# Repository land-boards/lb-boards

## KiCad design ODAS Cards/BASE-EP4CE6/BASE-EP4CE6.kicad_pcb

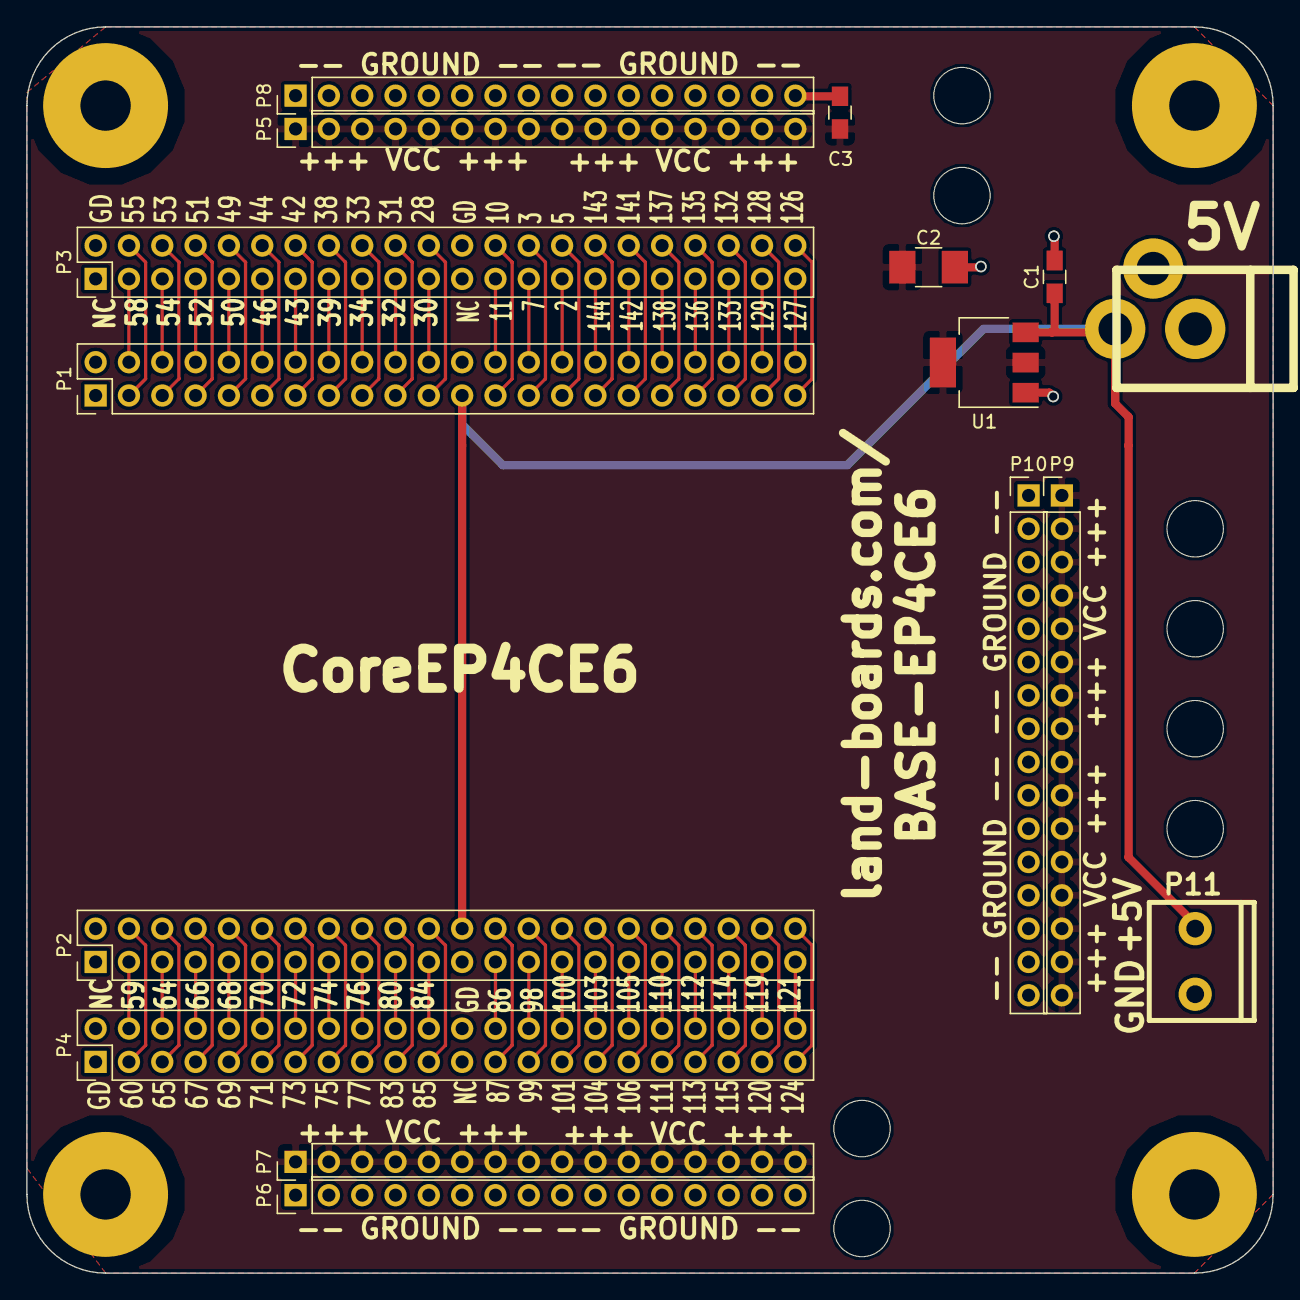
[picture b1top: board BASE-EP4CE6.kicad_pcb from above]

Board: 2 copper layers, 95.0 x 95.0 mm, 30 parts (0 on the bottom side), 83 nets.

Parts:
C1, C3: 0.1uF; C_0805_HandSoldering
C2: 10uF; C_1210_HandSoldering
COUP?1: COUPON; TEST_BLK-REAR
J1: DCJ0202; DCJ-NEW
MTG1, MTG2, MTG3: MTG_HOLE; MTG-6-32
MTG6, MTG7, MTG9, MTG10, MTG12, MTG13, MTG14, MTG15: MTG_HOLE; MountingHole_4.3mm_M4
MTG?1: MTG_HOLE; MTG-6-32
P1, P2, P3, P4: CONN_02X22; Pin_Header_Straight_2x22_Pitch2.54mm
P5, P6, P7, P8, P9, P10: CONN_01X16; Pin_Header_Straight_1x16_Pitch2.54mm
P11: CONN_01X02; TB2-5MM
TEST: COUPON; TEST_BLK-REAR
U1: AP1117; SOT-223

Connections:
+3V3: C2.1, C3.1, P5.1, P5.2, P5.3, P5.4, P5.5, P5.6, P5.7, P5.8, P5.9, P5.10, P5.11, P5.12, P5.13, P5.14, P5.15, P5.16, P7.1, P7.2, P7.3, P7.4, P7.5, P7.6, P7.7, P7.8, P7.9, P7.10, P7.11, P7.12, P7.13, P7.14, P7.15, P7.16, P9.1, P9.2, P9.3, P9.4, P9.5, P9.6, P9.7, P9.8, P9.9, P9.10, P9.11, P9.12, P9.13, P9.14, P9.15, P9.16, U1.2, U1.4
+5V: C1.1, J1.1, P1.23, P2.24, P11.1, U1.3
/P2: P1.30, P3.29
/P3: P1.27, P3.28
/P5: P1.29, P3.30
/P7: P1.28, P3.27
/P10: P1.25, P3.26
/P11: P1.26, P3.25
/P28: P1.21, P3.22
/P30: P1.22, P3.21
/P31: P1.19, P3.20
/P32: P1.20, P3.19
/P33: P1.17, P3.18
/P34: P1.18, P3.17
/P38: P1.15, P3.16
/P39: P1.16, P3.15
/P42: P1.13, P3.14
/P43: P1.14, P3.13
/P44: P1.11, P3.12
/P46: P1.12, P3.11
/P49: P1.9, P3.10
/P50: P1.10, P3.9
/P51: P1.7, P3.8
/P52: P1.8, P3.7
/P53: P1.5, P3.6
/P54: P1.6, P3.5
/P55: P1.3, P3.4
/P58: P1.4, P3.3
/P59: P2.3, P4.4
/P60: P2.4, P4.3
/P64: P2.5, P4.6
/P65: P2.6, P4.5
/P66: P2.7, P4.8
/P67: P2.8, P4.7
/P68: P2.9, P4.10
/P69: P2.10, P4.9
/P70: P2.11, P4.12
/P71: P2.12, P4.11
/P72: P2.13, P4.14
/P73: P2.14, P4.13
/P74: P2.15, P4.16
/P75: P2.16, P4.15
/P76: P2.17, P4.18
/P77: P2.18, P4.17
/P80: P2.19, P4.20
/P83: P2.20, P4.19
/P84: P2.21, P4.22
/P85: P2.22, P4.21
/P86: P2.25, P4.26
/P87: P2.26, P4.25
/P98: P2.27, P4.28
/P99: P2.28, P4.27
/P100: P2.29, P4.30
/P101: P2.30, P4.29
/P103: P2.31, P4.32
/P104: P2.32, P4.31
/P105: P2.33, P4.34
/P106: P2.34, P4.33
/P110: P2.35, P4.36
/P111: P2.36, P4.35
/P112: P2.37, P4.38
/P113: P2.38, P4.37
/P114: P2.39, P4.40
/P115: P2.40, P4.39
/P119: P2.41, P4.42
/P120: P2.42, P4.41
/P121: P2.43, P4.44
/P124: P2.44, P4.43
/P126: P1.43, P3.44
/P127: P1.44, P3.43
/P128: P1.41, P3.42
/P129: P1.42, P3.41
/P132: P1.39, P3.40
/P133: P1.40, P3.39
/P135: P1.37, P3.38
/P136: P1.38, P3.37
/P137: P1.35, P3.36
/P138: P1.36, P3.35
/P141: P1.33, P3.34
/P142: P1.34, P3.33
/P143: P1.31, P3.32
/P144: P1.32, P3.31
GND: C1.2, C2.2, C3.2, J1.2, J1.3, P1.2, P1.24, P2.1, P2.23, P3.2, P3.24, P4.1, P4.23, P6.1, P6.2, P6.3, P6.4, P6.5, P6.6, P6.7, P6.8, P6.9, P6.10, P6.11, P6.12, P6.13, P6.14, P6.15, P6.16, P8.1, P8.2, P8.3, P8.4, P8.5, P8.6, P8.7, P8.8, P8.9, P8.10, P8.11, P8.12, P8.13, P8.14, P8.15, P8.16, P10.1, P10.2, P10.3, P10.4, P10.5, P10.6, P10.7, P10.8, P10.9, P10.10, P10.11, P10.12, P10.13, P10.14, P10.15, P10.16, P11.2, U1.1

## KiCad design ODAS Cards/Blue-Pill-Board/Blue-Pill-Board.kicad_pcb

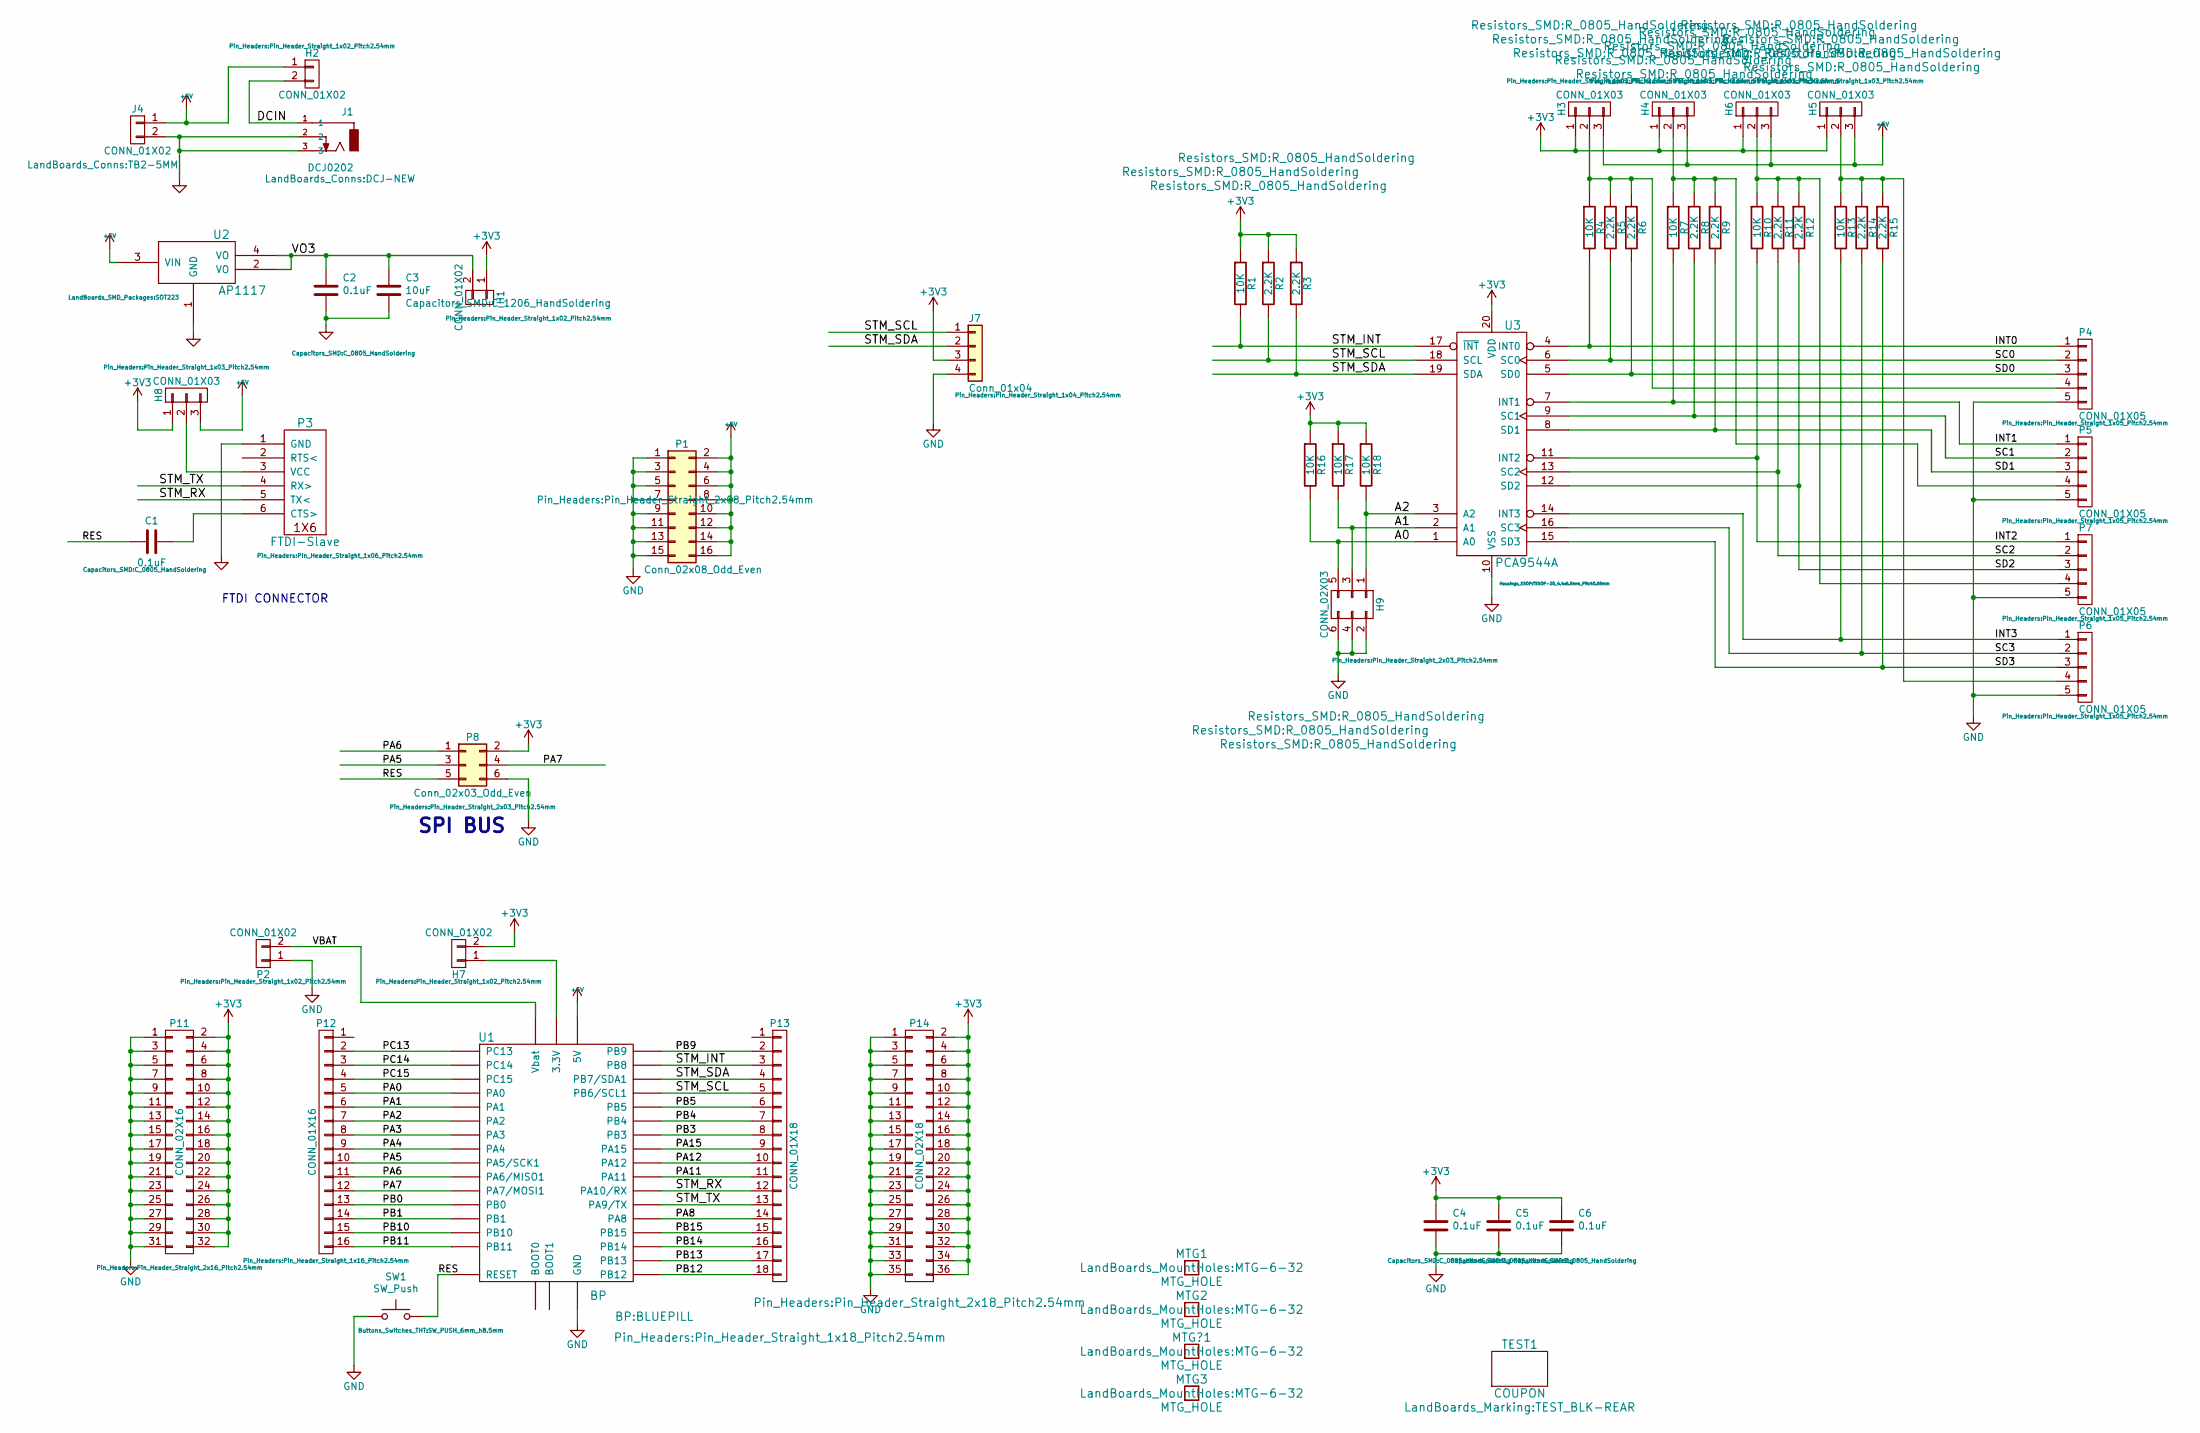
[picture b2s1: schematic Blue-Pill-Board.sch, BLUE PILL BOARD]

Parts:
C1, C2, C4, C5, C6: 0.1uF; C_0805_HandSoldering
C3: 10uF; C_1206_HandSoldering
H1, H2, H7: CONN_01X02; Pin_Header_Straight_1x02_Pitch2.54mm
H3, H4, H5, H6, H8: CONN_01X03; Pin_Header_Straight_1x03_Pitch2.54mm
H9: CONN_02X03; Pin_Header_Straight_2x03_Pitch2.54mm
J1: DCJ0202; DCJ-NEW
J4: CONN_01X02; TB2-5MM
J7: Conn_01x04; Pin_Header_Straight_1x04_Pitch2.54mm
MTG1, MTG2, MTG3: MTG_HOLE; MTG-6-32
MTG?1: MTG_HOLE; MTG-6-32
P1: Conn_02x08_Odd_Even; Pin_Header_Straight_2x08_Pitch2.54mm
P2: CONN_01X02; Pin_Header_Straight_1x02_Pitch2.54mm
P3: FTDI-Slave; Pin_Header_Straight_1x06_Pitch2.54mm
P4, P5, P6, P7: CONN_01X05; Pin_Header_Straight_1x05_Pitch2.54mm
P8: Conn_02x03_Odd_Even; Pin_Header_Straight_2x03_Pitch2.54mm
P11: CONN_02X16; Pin_Header_Straight_2x16_Pitch2.54mm
P12: CONN_01X16; Pin_Header_Straight_1x16_Pitch2.54mm
P13: CONN_01X18; Pin_Header_Straight_1x18_Pitch2.54mm
P14: CONN_02X18; Pin_Header_Straight_2x18_Pitch2.54mm
R1, R4, R7, R10, R13, R16, R17, R18: 10K; R_0805_HandSoldering
R2, R3, R5, R6, R8, R9, R11, R12, R14, R15: 2.2K; R_0805_HandSoldering
SW1: SW_Push; SW_PUSH_6mm_h8.5mm
TEST1: COUPON; TEST_BLK-REAR
U1: BP; BLUEPILL
U2: AP1117; SOT223
U3: PCA9544A; TSSOP-20_4.4x6.5mm_Pitch0.65mm

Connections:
+3V3: C4.1, C5.1, C6.1, H1.1, H3.1, H4.1, H5.1, H6.1, H7.2, H8.1, J7.3, P8.2, P11.2, P11.4, P11.6, P11.8, P11.10, P11.12, P11.14, P11.16, P11.18, P11.20, P11.22, P11.24, P11.26, P11.28, P11.30, P11.32, P14.2, P14.4, P14.6, P14.8, P14.10, P14.12, P14.14, P14.16, P14.18, P14.20, P14.22, P14.24, P14.26, P14.28, P14.30, P14.32, P14.34, P14.36, R1.1, R2.1, R3.1, R16.1, R17.1, R18.1, U3.20 (VDD)
+5V: H2.1, H3.3, H4.3, H5.3, H6.3, H8.3, J4.1, P1.2, P1.4, P1.6, P1.8, P1.10, P1.12, P1.14, P1.16, U1.5V, U2.3 (VIN)
/A0: H9.5, R16.2, U3.1 (A0)
/A1: H9.3, R17.2, U3.2 (A1)
/A2: H9.1, R18.2, U3.3 (A2)
/DCIN: H2.2, J1.1
/INT0: P4.1, R4.2, U3.4 (INT0)
/INT1: P5.1, R7.2, U3.7 (INT1)
/INT2: P7.1, R10.2, U3.11 (INT2)
/INT3: P6.1, R13.2, U3.14 (INT3)
/PA0: P12.5, U1.PA0
/PA1: P12.6, U1.PA1
/PA2: P12.7, U1.PA2
/PA3: P12.8, U1.PA3
/PA4: P12.9, U1.PA4
/PA5: P8.3, P12.10, U1.PA5 (PA5/SCK1)
/PA6: P8.1, P12.11, U1.PA6 (PA6/MISO1)
/PA7: P8.4, P12.12, U1.PA7 (PA7/MOSI1)
/PA8: P13.14, U1.PA8
/PA11: P13.11, U1.PA11
/PA12: P13.10, U1.PA12
/PA15: P13.9, U1.PA15
/PB0: P12.13, U1.PB0
/PB1: P12.14, U1.PB1
/PB3: P13.8, U1.PB3
/PB4: P13.7, U1.PB4
/PB5: P13.6, U1.PB5
/PB9: P13.2, U1.PB9
/PB10: P12.15, U1.PB10
/PB11: P12.16, U1.PB11
/PB12: P13.18, U1.PB12
/PB13: P13.17, U1.PB13
/PB14: P13.16, U1.PB14
/PB15: P13.15, U1.PB15
/PC13: P12.2, U1.PC13
/PC14: P12.3, U1.PC14
/PC15: P12.4, U1.PC15
/RES: C1.2, P8.5, SW1.2, U1.NRST (RESET)
/SC0: P4.2, R5.2, U3.6 (SC0)
/SC1: P5.2, R8.2, U3.9 (SC1)
/SC2: P7.2, R11.2, U3.13 (SC2)
/SC3: P6.2, R14.2, U3.16 (SC3)
/SD0: P4.3, R6.2, U3.5 (SD0)
/SD1: P5.3, R9.2, U3.8 (SD1)
/SD2: P7.3, R12.2, U3.12 (SD2)
/SD3: P6.3, R15.2, U3.15 (SD3)
/STM_INT: P13.3, R1.2, U1.PB8, U3.17 (~INT)
/STM_RX: P3.5 (TX<), P13.12, U1.PA10 (PA10/RX)
/STM_SCL: J7.1, P13.5, R2.2, U1.PB6 (PB6/SCL1), U3.18 (SCL)
/STM_SDA: J7.2, P13.4, R3.2, U1.PB7 (PB7/SDA1), U3.19 (SDA)
/STM_TX: P3.4 (RX>), P13.13, U1.PA9 (PA9/TX)
/VBAT: P2.2, U1.VBAT (Vbat)
/VO3: C2.1, C3.1, H1.2, U2.2 (VO), U2.4 (VO)
GND: C2.2, C3.2, C4.2, C5.2, C6.2, H9.2, H9.4, H9.6, J1.2, J1.3, J4.2, J7.4, P1.1, P1.3, P1.5, P1.7, P1.9, P1.11, P1.13, P1.15, P2.1, P3.1 (GND), P4.5, P5.5, P6.5, P7.5, P8.6, P11.1, P11.3, P11.5, P11.7, P11.9, P11.11, P11.13, P11.15, P11.17, P11.19, P11.21, P11.23, P11.25, P11.27, P11.29, P11.31, P14.1, P14.3, P14.5, P14.7, P14.9, P14.11, P14.13, P14.15, P14.17, P14.19, P14.21, P14.23, P14.25, P14.27, P14.29, P14.31, P14.33, P14.35, SW1.1, U1.G (GND), U2.1 (GND), U3.10 (VSS)
unnamed: C1.1, P3.6 (CTS>)
unnamed: H3.2, P4.4, R4.1, R5.1, R6.1
unnamed: H4.2, P5.4, R7.1, R8.1, R9.1
unnamed: H5.2, P6.4, R13.1, R14.1, R15.1
unnamed: H6.2, P7.4, R10.1, R11.1, R12.1
unnamed: H7.1, U1.3V3 (3.3V)
unnamed: H8.2, P3.3 (VCC)

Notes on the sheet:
FTDI CONNECTOR
SPI BUS

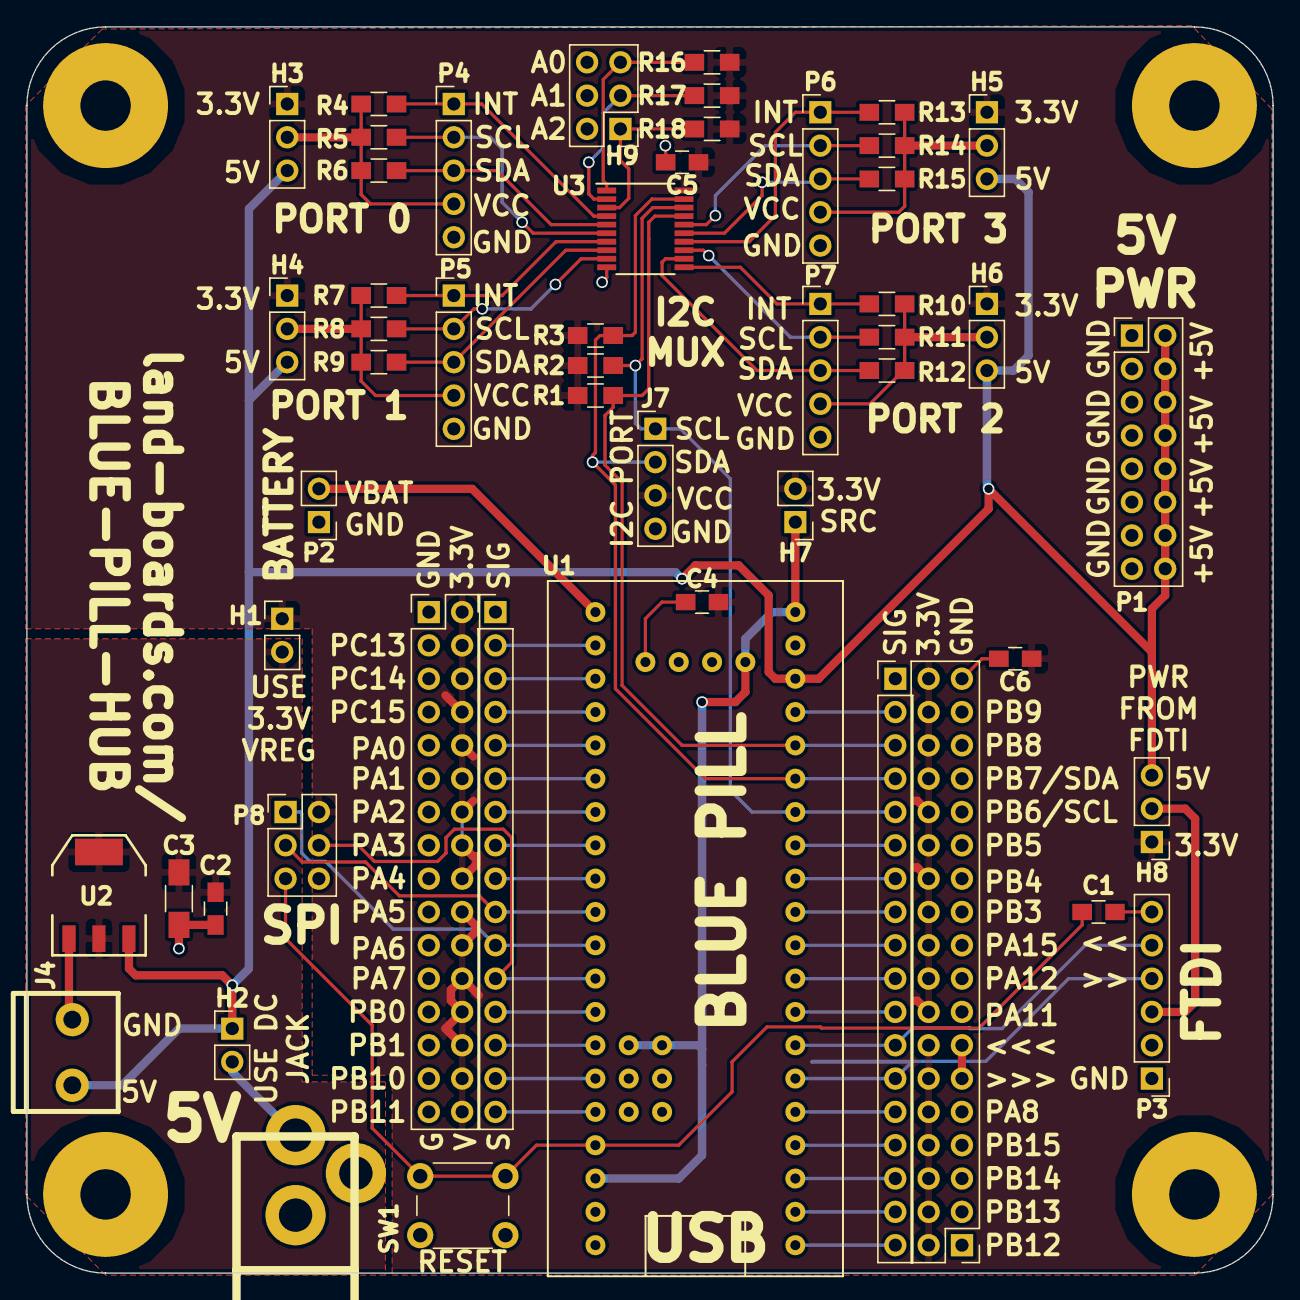
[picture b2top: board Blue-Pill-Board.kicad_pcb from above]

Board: 2 copper layers, 95.0 x 95.0 mm, 57 parts (0 on the bottom side), 61 nets.

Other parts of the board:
TEST: COUPON; TEST_BLK-REAR

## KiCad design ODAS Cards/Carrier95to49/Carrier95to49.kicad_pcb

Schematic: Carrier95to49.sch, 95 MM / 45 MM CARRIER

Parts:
D1: LED_ALT; LED_D5.0mm
H1: CONN_02X16; Pin_Header_Angled_2x16_Pitch2.54mm
H2, H3: CONN_02X16; Pin_Header_Straight_2x16_Pitch2.54mm
J1: DCJ0202; DCJ-NEW
MTG1, MTG2, MTG3, MTG16, MTG17: MTG_HOLE; MTG-6-32
MTG4, MTG5, MTG6, MTG7, MTG8, MTG9, MTG10, MTG11, MTG12, MTG13, MTG14, MTG15: MTG_HOLE; MountingHole_4.3mm_M4
MTG?1: MTG_HOLE; MTG-6-32
P1: 49MM; TEST_BLK-REAR
P8: CONN_01X02; TB2-5MM
R1: 560; R_0805_2012Metric_Pad1.15x1.40mm_HandSolder
SW1: SW_SPDT; PinHeader_1x03_P2.54mm_Vertical
TEST1: COUPON; BD-49X49

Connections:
+5V: H1.1, H1.3, H1.5, H1.7, H1.9, H1.11, H1.13, H1.15, H1.17, H1.19, H1.21, H1.23, H1.25, H1.27, H1.29, H1.31, H2.1, H2.3, H2.5, H2.7, H2.9, H2.11, H2.13, H2.15, H2.17, H2.19, H2.21, H2.23, H2.25, H2.27, H2.29, H2.31, H3.1, H3.3, H3.5, H3.7, H3.9, H3.11, H3.13, H3.15, H3.17, H3.19, H3.21, H3.23, H3.25, H3.27, H3.29, H3.31, R1.1, SW1.1
GND: D1.1, H1.2, H1.4, H1.6, H1.8, H1.10, H1.12, H1.14, H1.16, H1.18, H1.20, H1.22, H1.24, H1.26, H1.28, H1.30, H1.32, H2.2, H2.4, H2.6, H2.8, H2.10, H2.12, H2.14, H2.16, H2.18, H2.20, H2.22, H2.24, H2.26, H2.28, H2.30, H2.32, H3.2, H3.4, H3.6, H3.8, H3.10, H3.12, H3.14, H3.16, H3.18, H3.20, H3.22, H3.24, H3.26, H3.28, H3.30, H3.32, J1.2, J1.3, P8.2
unnamed: D1.2, R1.2
unnamed: J1.1, P8.1, SW1.2

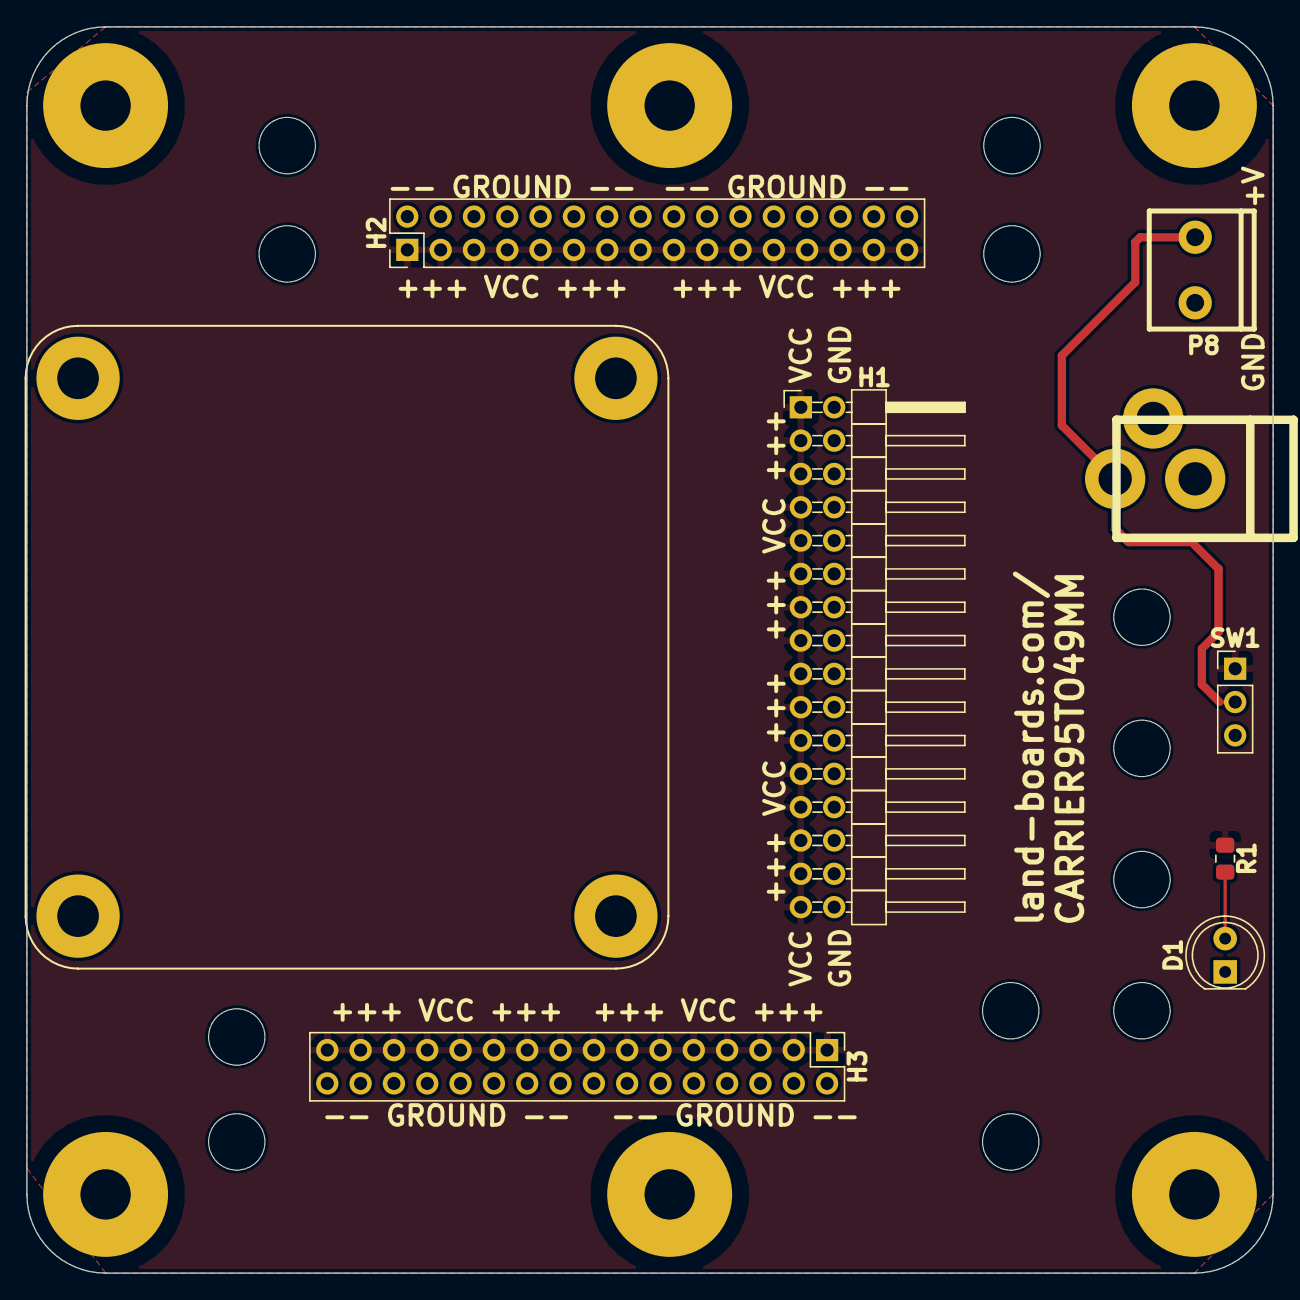
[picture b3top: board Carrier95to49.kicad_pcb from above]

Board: 2 copper layers, 95.0 x 95.0 mm, 28 parts (0 on the bottom side), 4 nets.

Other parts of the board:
TEST: 49MM; TEST_BLK-REAR

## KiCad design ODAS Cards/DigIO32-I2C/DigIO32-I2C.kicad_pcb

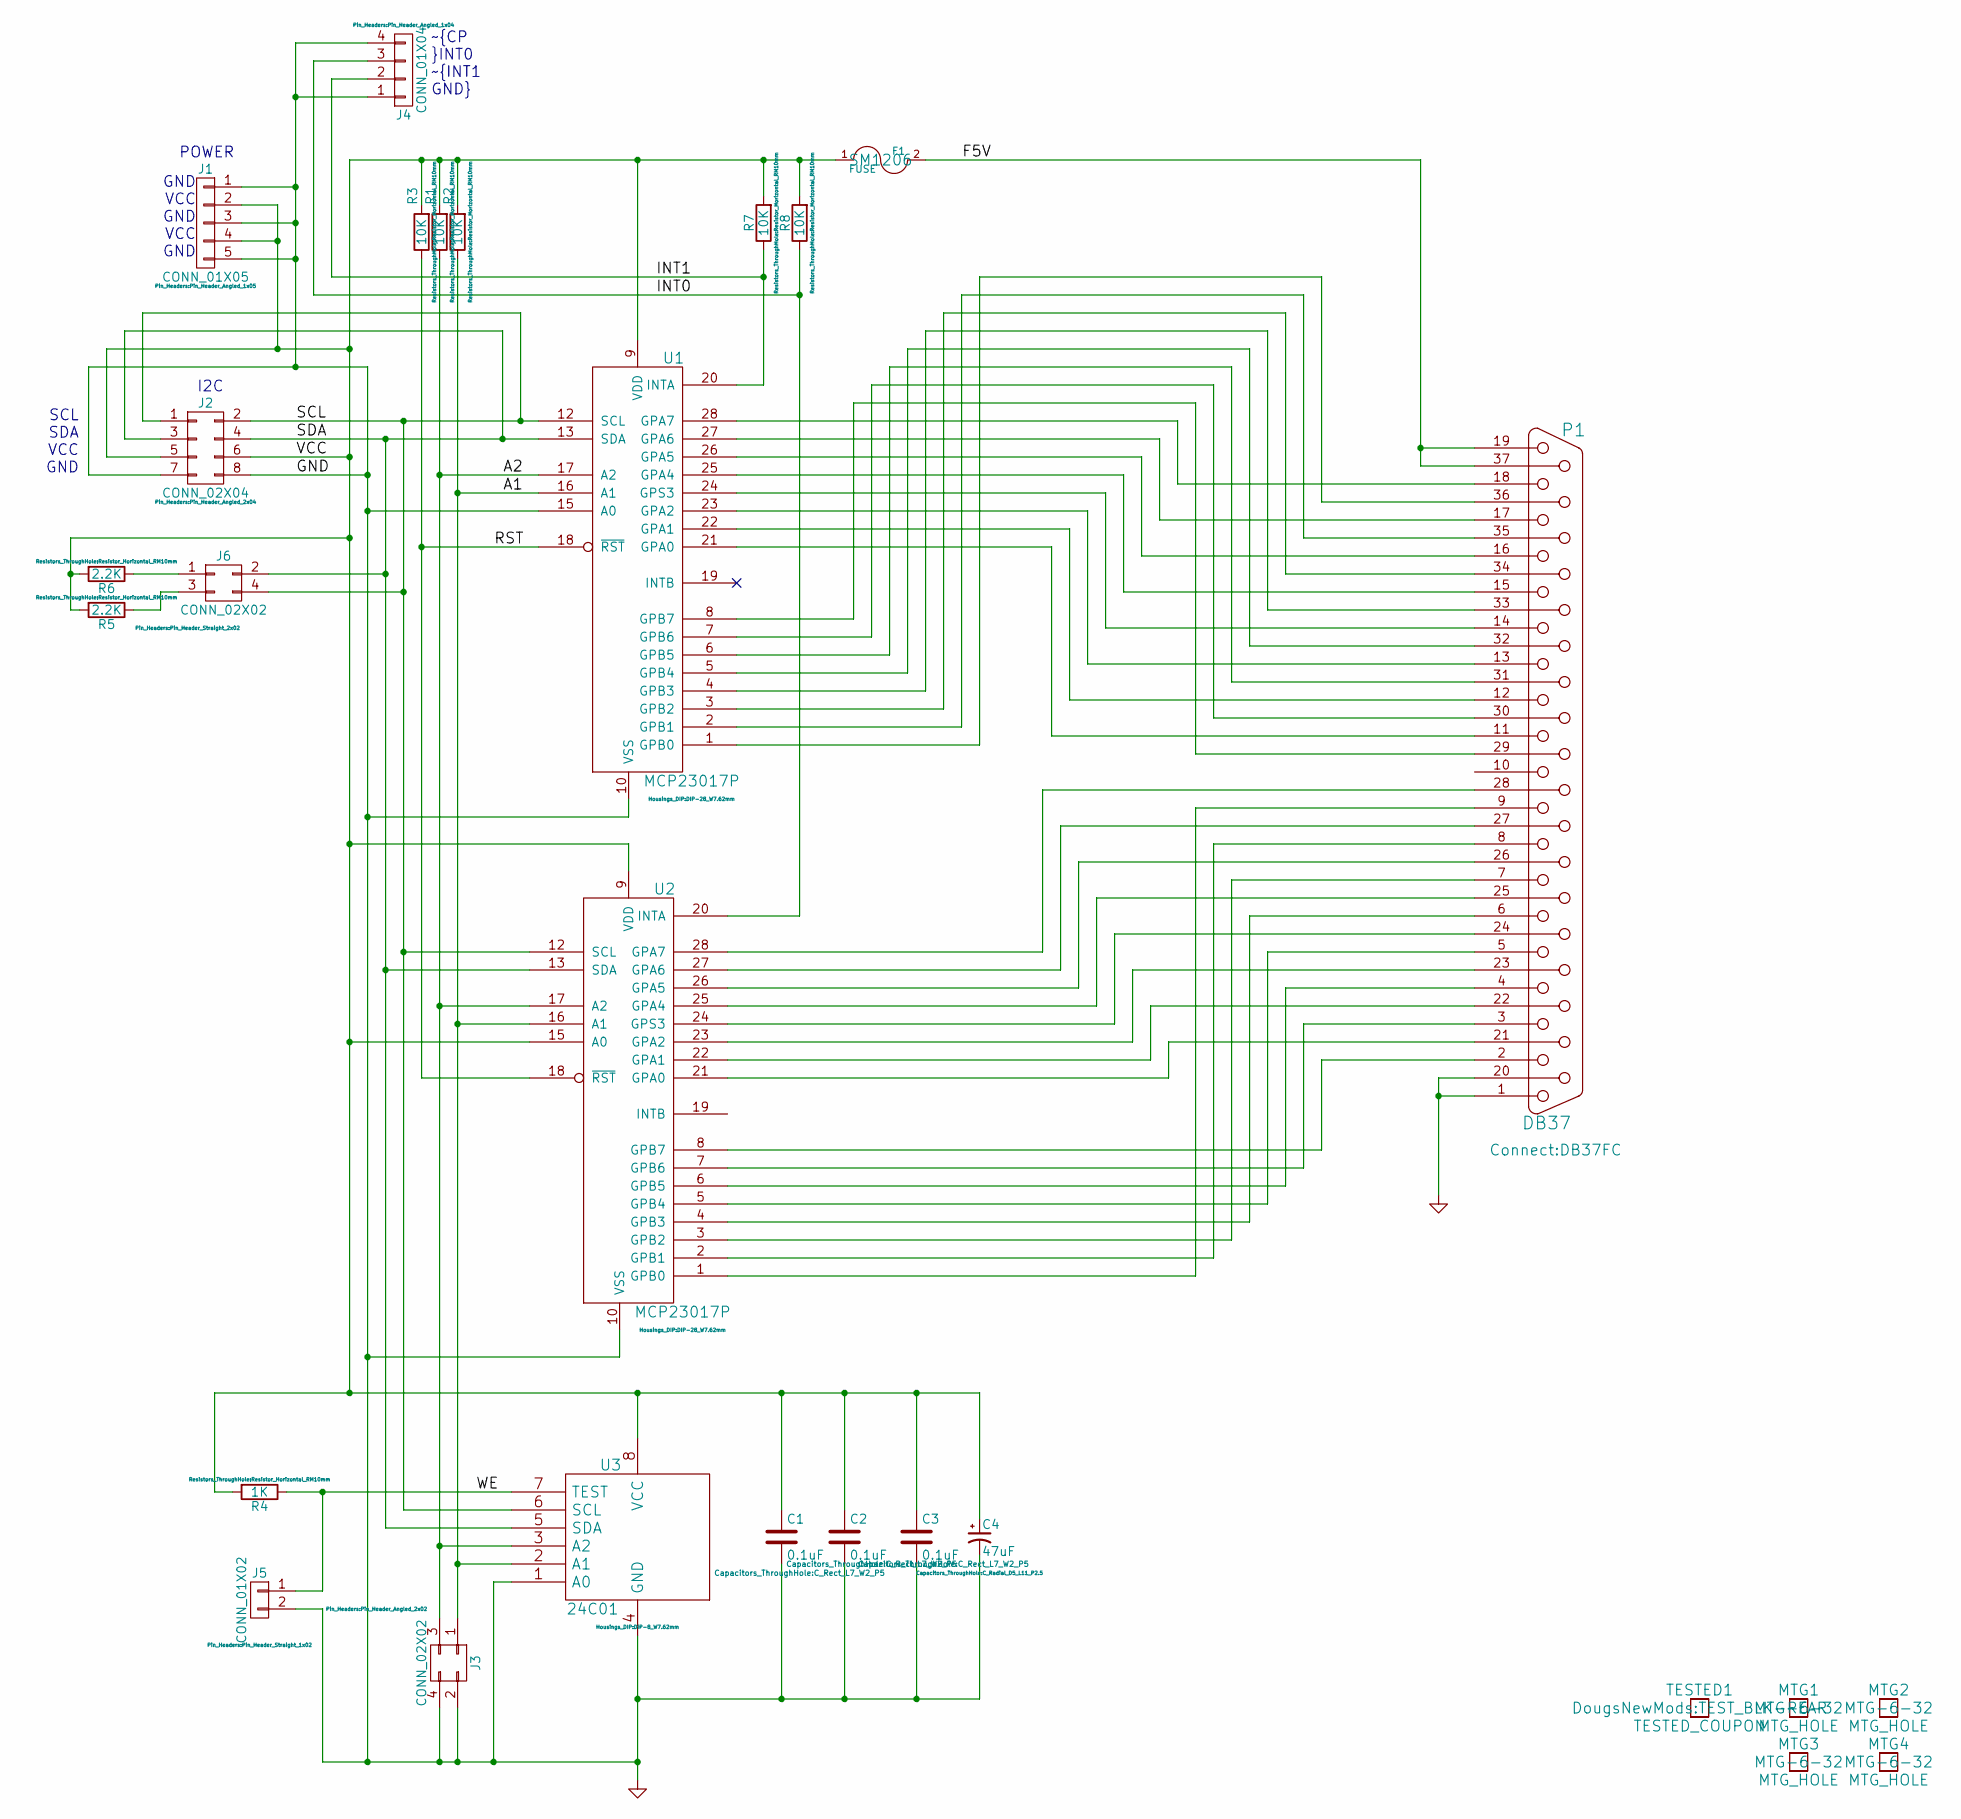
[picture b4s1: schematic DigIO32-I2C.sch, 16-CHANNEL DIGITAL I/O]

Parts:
C1, C2, C3: 0.1uF; C_Rect_L7_W2_P5
C4: 47uF; C_Radial_D5_L11_P2.5
F1: FUSE; SM1206
J1: CONN_01X05; Pin_Header_Angled_1x05
J2: CONN_02X04; Pin_Header_Angled_2x04
J3: CONN_02X02; Pin_Header_Angled_2x02
J4: CONN_01X04; Pin_Header_Angled_1x04
J5: CONN_01X02; Pin_Header_Straight_1x02
J6: CONN_02X02; Pin_Header_Straight_2x02
MTG1, MTG2, MTG3, MTG4: MTG_HOLE; MTG-6-32
P1: DB37; DB37FC
R1, R2, R3, R7, R8: 10K; Resistor_Horizontal_RM10mm
R4: 1K; Resistor_Horizontal_RM10mm
R5, R6: 2.2K; Resistor_Horizontal_RM10mm
TESTED1: TESTED_COUPON; TEST_BLK-REAR
U1, U2: MCP23017P; DIP-28_W7.62mm
U3: 24C01; DIP-8_W7.62mm

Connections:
/A1: J3.1, R2.1, U1.16 (A1), U2.16 (A1), U3.2 (A1)
/A2: J3.3, R1.1, U1.17 (A2), U2.17 (A2), U3.3 (A2)
/C0GPA0: P1.11, U1.21 (GPA0)
/C0GPA1: P1.12, U1.22 (GPA1)
/C0GPA2: P1.13, U1.23 (GPA2)
/C0GPA3: P1.14, U1.24 (GPS3)
/C0GPA4: P1.15, U1.25 (GPA4)
/C0GPA5: P1.16, U1.26 (GPA5)
/C0GPA6: P1.17, U1.27 (GPA6)
/C0GPA7: P1.18, U1.28 (GPA7)
/C0GPB0: P1.36, U1.1 (GPB0)
/C0GPB1: P1.35, U1.2 (GPB1)
/C0GPB2: P1.34, U1.3 (GPB2)
/C0GPB3: P1.33, U1.4 (GPB3)
/C0GPB4: P1.32, U1.5 (GPB4)
/C0GPB5: P1.31, U1.6 (GPB5)
/C0GPB6: P1.30, U1.7 (GPB6)
/C0GPB7: P1.29, U1.8 (GPB7)
/C1GPA0: P1.21, U2.21 (GPA0)
/C1GPA1: P1.22, U2.22 (GPA1)
/C1GPA2: P1.23, U2.23 (GPA2)
/C1GPA3: P1.24, U2.24 (GPS3)
/C1GPA4: P1.25, U2.25 (GPA4)
/C1GPA5: P1.26, U2.26 (GPA5)
/C1GPA6: P1.27, U2.27 (GPA6)
/C1GPA7: P1.28, U2.28 (GPA7)
/C1GPB0: P1.9, U2.1 (GPB0)
/C1GPB1: P1.8, U2.2 (GPB1)
/C1GPB2: P1.7, U2.3 (GPB2)
/C1GPB3: P1.6, U2.4 (GPB3)
/C1GPB4: P1.5, U2.5 (GPB4)
/C1GPB5: P1.4, U2.6 (GPB5)
/C1GPB6: P1.3, U2.7 (GPB6)
/C1GPB7: P1.2, U2.8 (GPB7)
/F5V: F1.2, P1.19, P1.37
/INT0: J4.3, R8.1, U2.20 (INTA)
/INT1: J4.2, R7.1, U1.20 (INTA)
/RST: R3.1, U1.18 (~RST), U2.18 (~RST)
/SCL: J2.1, J2.2, J6.4, U1.12 (SCL), U2.12 (SCL), U3.6 (SCL)
/SDA: J2.3, J2.4, J6.2, U1.13 (SDA), U2.13 (SDA), U3.5 (SDA)
/VCC: C1.1, C2.1, C3.1, C4.1, F1.1, J1.2, J1.4, J2.5, J2.6, R1.2, R2.2, R3.2, R4.2, R5.2, R6.2, R7.2, R8.2, U1.9 (VDD), U2.9 (VDD), U2.15 (A0), U3.8 (VCC)
/WE: J5.1, R4.1, U3.7 (TEST)
GND: C1.2, C2.2, C3.2, C4.2, J1.1, J1.3, J1.5, J2.7, J2.8, J3.2, J3.4, J4.1, J4.4, J5.2, P1.1, P1.20, U1.10 (VSS), U1.15 (A0), U2.10 (VSS), U3.1 (A0), U3.4 (GND)
unnamed: J6.1, R6.1
unnamed: J6.3, R5.1

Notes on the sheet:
SCL SDA VCC GND
GND VCC GND VCC GND
~CP ~INT0 ~INT1 GND
POWER
I2C

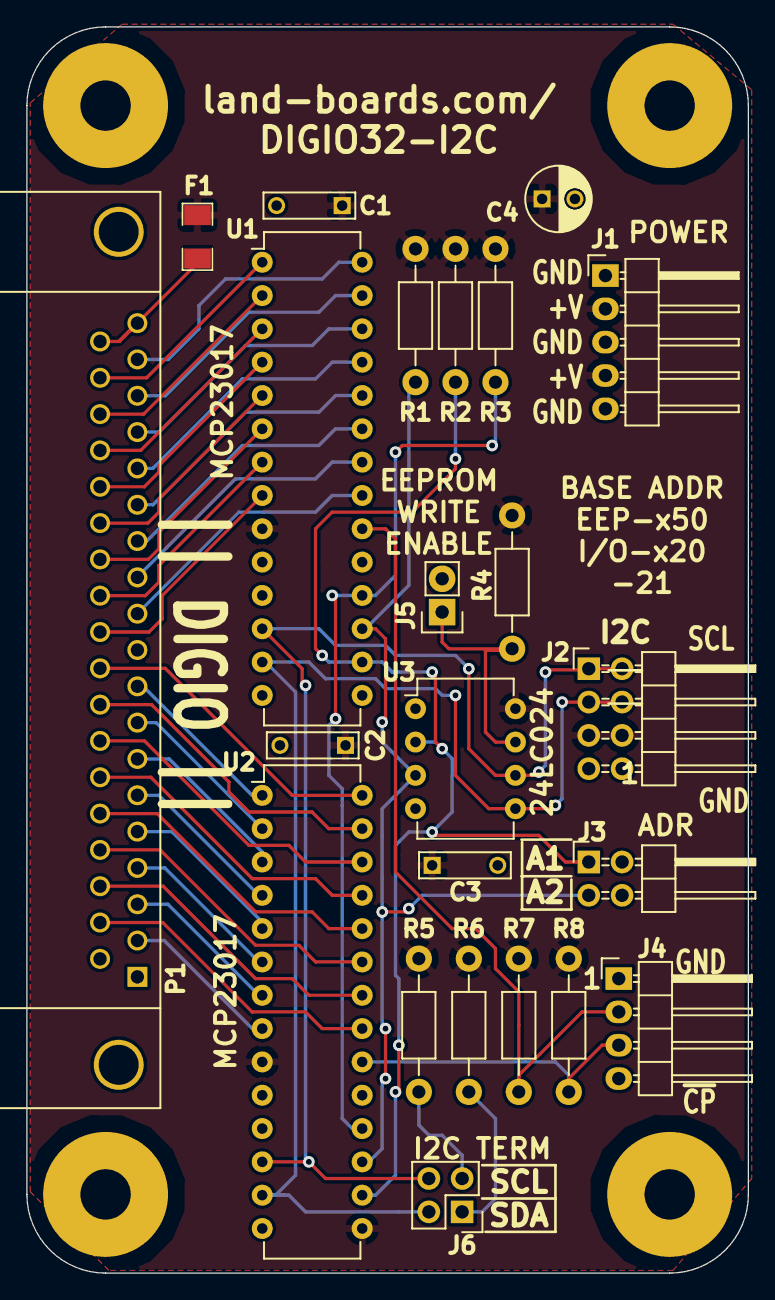
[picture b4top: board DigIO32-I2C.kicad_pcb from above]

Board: 2 copper layers, 55.0 x 95.0 mm, 28 parts (0 on the bottom side), 45 nets.

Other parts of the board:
TESTED: TESTED_COUPON; TEST_BLK-REAR

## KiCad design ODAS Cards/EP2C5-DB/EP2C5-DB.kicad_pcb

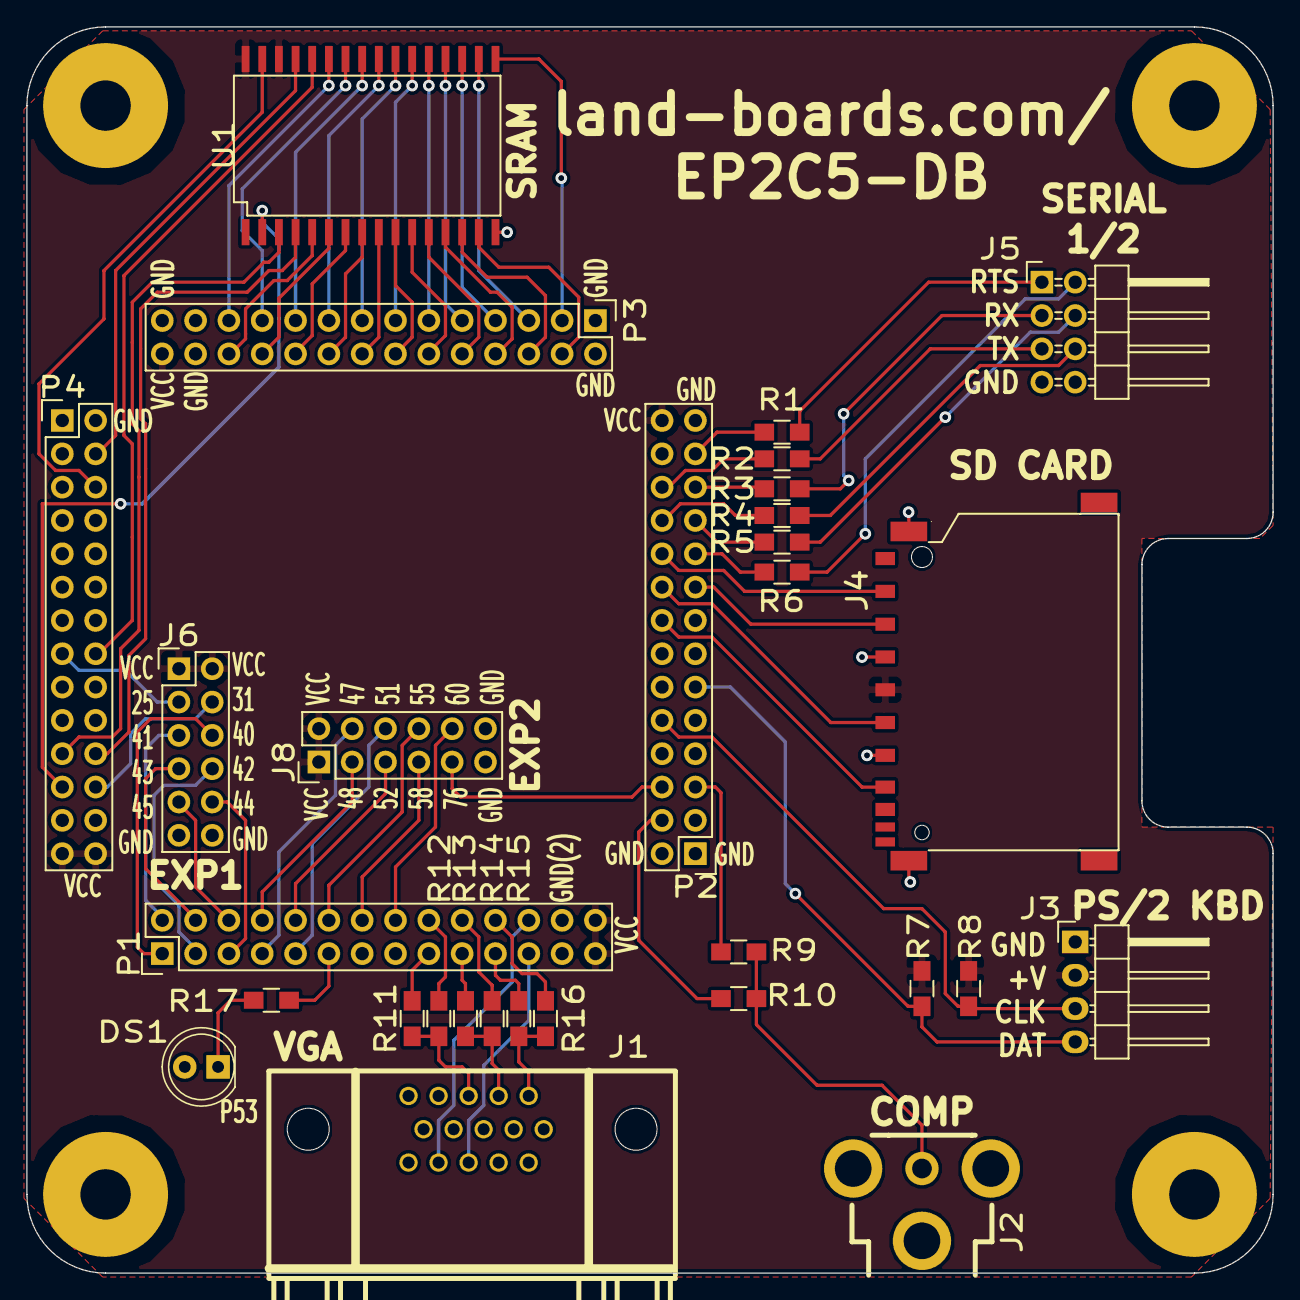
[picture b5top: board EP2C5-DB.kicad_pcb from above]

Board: 2 copper layers, 95.0 x 95.0 mm, 35 parts (0 on the bottom side), 80 nets.

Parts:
DS1: LED; LED_D5.0mm
J1: VGA; DB_15F-VGA-fixed
J2: RCA-JACK; RCA
J3: CONN_01X04; Pin_Header_Angled_1x04
J4: SD_Card; SD_CARD
J5: CONN_02X04; Pin_Header_Angled_2x04
J6, J8: CONN_02X06; Pin_Header_Straight_2x06
MTG1, MTG2, MTG3, MTG4: MTG_HOLE; MTG-6-32
P1, P2, P3, P4: CONN_02X14; Pin_Header_Straight_2x14
R1, R2, R3, R4, R5, R6: 2.7K; R_0805_HandSoldering
R7, R8: 10K; R_0805_HandSoldering
R9, R11, R13, R15: 470; R_0805_HandSoldering
R10: 1K; R_0805_HandSoldering
R12, R14, R16: 680; R_0805_HandSoldering
R17: 220; R_0805_HandSoldering
TESTED: TESTED_COUPON; TEST_BLK-REAR
U1: AS6C1008; SOP32

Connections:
/P4: P4.4, U1.29
/P8: P4.6, U1.31
/P24: P4.16, U1.28
/P25: J6.3, P4.15
/P28: P4.22, U1.4
/P30: P4.21, U1.3
/P31: J6.4, P4.24
/P32: P4.23, U1.2
/P40: J6.6, P1.1
/P41: J6.5, P1.2
/P42: J6.8, P1.3
/P43: J6.7, P1.4
/P44: J6.10, P1.5
/P45: J6.9, P1.6
/P47: J8.4, P1.7
/P48: J8.3, P1.8
/P51: J8.6, P1.9
/P52: J8.5, P1.10
/P53: P1.11, R17.1
/P55: J8.8, P1.12
/P58: J8.7, P1.14
/P60: J8.10, P1.16
/P63: P1.17, R11.1
/P64: P1.18, R12.1
/P65: P1.19, R13.1
/P67: P1.20, R14.1
/P69: P1.21, R15.1
/P70: P1.22, R16.1
/P71: J1.13, P1.23
/P72: J1.14, P1.24
/P74: P2.4, R10.1
/P75: P2.5, R9.1
/P76: J8.9, P2.6
/P86: J3.3, P2.10, R8.2
/P87: J3.4, P2.11, R7.2
/P92: J4.7, P2.16
/P93: J4.2, P2.17
/P94: J4.5, P2.18
/P96: P2.19, R6.2
/P97: J4.1, P2.20
/P99: P2.21, R5.2
/P100: P2.22, R4.2
/P101: P2.23, R3.1
/P103: P2.24, R2.1
/P104: P2.25, R1.1
/P112: P3.3, U1.17
/P113: P3.4, U1.15
/P114: P3.5, U1.18
/P115: P3.6, U1.14
/P118: P3.7, U1.19
/P119: P3.8, U1.13
/P120: P3.9, U1.20
/P121: P3.10, U1.12
/P122: P3.11, U1.21
/P125: P3.12, U1.11
/P126: P3.13, U1.22
/P129: P3.14, U1.10
/P132: P3.15, U1.23
/P133: P3.16, U1.9
/P134: P3.17, U1.24
/P135: P3.18, U1.8
/P136: P3.19, U1.25
/P137: P3.20, U1.7
/P139: P3.21, U1.26
/P141: P3.22, U1.6
/P142: P3.23, U1.27
/P143: P3.24, U1.5
/RTS1: J5.1, R1.2
/RTS2: J5.2, R6.1
/RX1: J5.3, R3.2
/RX2: J5.4, R5.1
/TX1: J5.5, R2.2
/TX2: J5.6, R4.1
GND: DS1.2, J1.5, J1.6, J1.7, J1.8, J1.10, J2.1, J2.2, J2.3, J3.1, J4.3, J4.6, J4.12, J4.13, J5.7, J5.8, J6.11, J6.12, J8.11, J8.12, P1.25, P1.26, P2.1, P2.2, P2.26, P2.27, P3.1, P3.2, P3.26, P3.27, P4.1, P4.2, P4.8, P4.9, P4.10, P4.25, P4.26, U1.16
unnamed: DS1.1, R17.2
unnamed: J1.1, R15.2, R16.2
unnamed: J1.2, R13.2, R14.2
unnamed: J1.3, R11.2, R12.2
unnamed: J2.4, R9.2, R10.2
VCC: J3.2, J4.4, J6.1, J6.2, J8.1, J8.2, P1.27, P1.28, P2.28, P3.28, P4.27, P4.28, R7.1, R8.1, U1.30, U1.32
